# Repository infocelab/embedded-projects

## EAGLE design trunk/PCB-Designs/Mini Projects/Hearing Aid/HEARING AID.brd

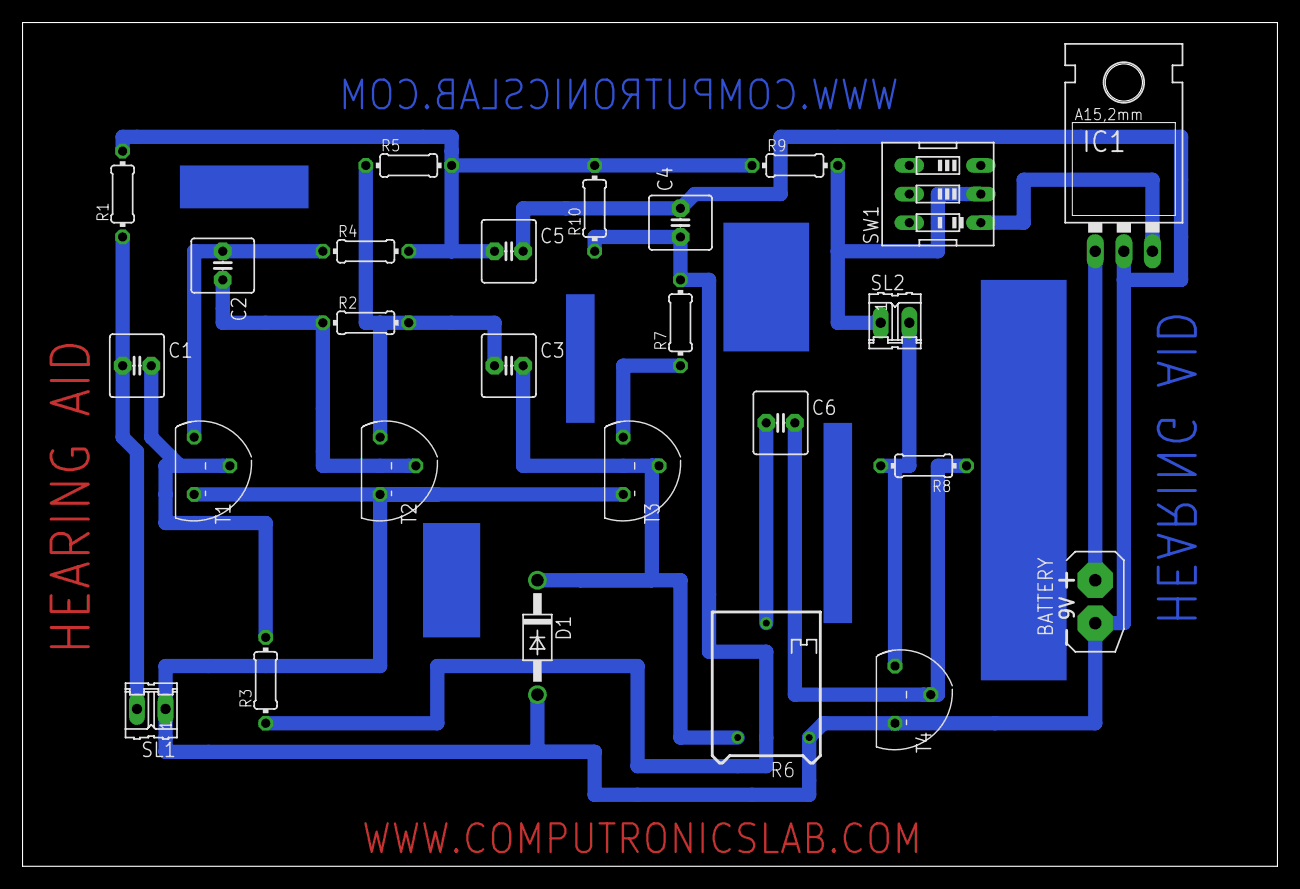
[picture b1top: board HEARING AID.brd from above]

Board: 2 copper layers, 111.4 x 74.9 mm, 26 parts (0 on the bottom side), 16 nets.

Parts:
BATTERY: 9V; AB9V
C1, C2: 0.1uf; C2.5-6
C3, C6: 1uf; C2.5-6
C4: 10uf; C2.5-6
C5: 100uf; C2.5-6
D1: 1N4007; DO41-10
IC1: 7805; 78XXL
R1, R8: 10K; 0204/7
R2, R10: 100k; 0204/7
R3: 1M; 0204/7
R4: 4.7K; 0204/7
R5: 3.9K; 0204/7
R6: 22K; RTRIM64P
R7: 1.5K; 0204/7
R9: 100E; 0204/7
SL1: electret mic; 02P
SL2: ear phone; 02P
SW1: on/off switch; EDG-03
T1, T2, T3, T4: BC547; TO92

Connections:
unnamed: C1.2, R3.2, T1.2
unnamed: C1.1, R1.1, SL1.2
unnamed: C2.1, R4.1, T1.3
unnamed: C2.2, R2.1, T2.2
unnamed: C3.1, R2.2, R5.1, T2.3
unnamed: C3.2, D1.C, R6.3, T3.2
unnamed: R7.1, T3.3
unnamed: C4.1, R3.1, R7.2, R10.1
unnamed: C5.1, R1.2, R4.2, R5.2, R9.1, R10.2
unnamed: C6.1, R6.2
unnamed: C6.2, R8.1, T4.2
unnamed: R8.2, SL2.2, T4.3
unnamed: BATTERY.+, IC1.IN
unnamed: BATTERY.-, C4.2, C5.2, D1.A, IC1.GND, R6.1, SL1.1, T1.1, T2.1, T3.1, T4.1
unnamed: IC1.OUT, SW1.1
unnamed: R9.2, SL2.1, SW1.2

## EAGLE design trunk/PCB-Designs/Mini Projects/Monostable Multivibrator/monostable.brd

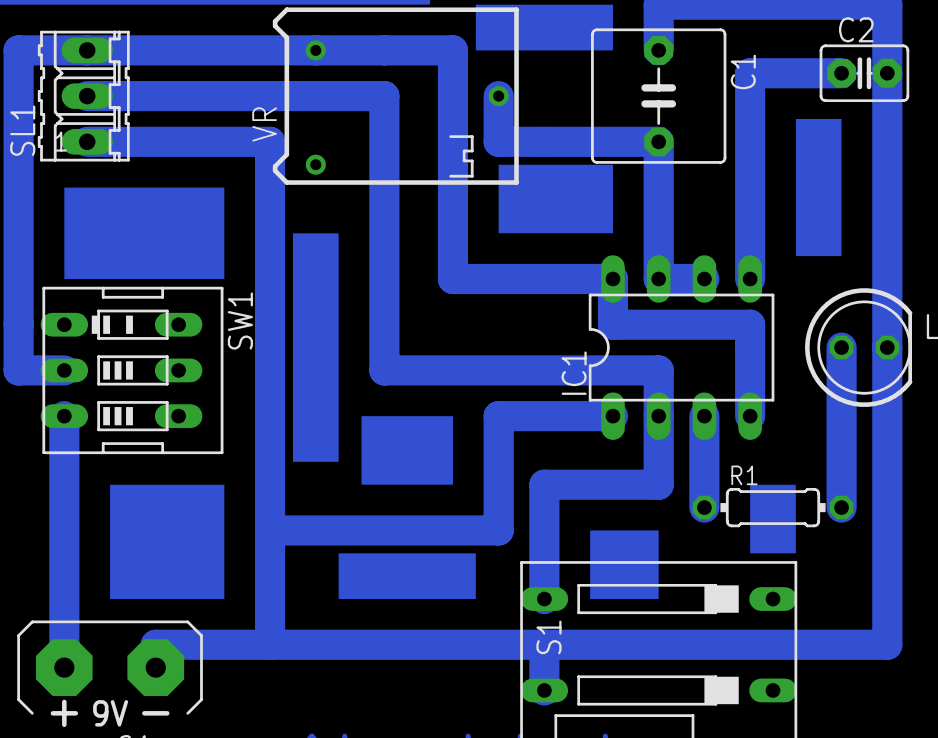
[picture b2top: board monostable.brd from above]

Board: 2 copper layers, 10 parts (0 on the bottom side), 8 nets.

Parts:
C1: 100uf; C5B7.2
C2: 0.1uf; C2.5-3
G1: AB9V
IC1: NE555; DIL-08
LED1: 5mm; LED5MM
R1: 330E; 0204/7
S1: push switch; DS-02
SL1: 03P
SW1: on/off switch; EDG-03
VR: 100k; RTRIM64P

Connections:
unnamed: C1.2, IC1.6, IC1.7, VR.2
unnamed: IC1.2, S1.3, SL1.2
unnamed: C2.1, IC1.5
unnamed: IC1.3, R1.1
unnamed: LED1.A, R1.2
unnamed: G1.+, SW1.3
unnamed: C1.1, C2.2, G1.-, IC1.1, LED1.K, S1.4, SL1.1
unnamed: IC1.4, IC1.8, SL1.3, SW1.2, VR.3

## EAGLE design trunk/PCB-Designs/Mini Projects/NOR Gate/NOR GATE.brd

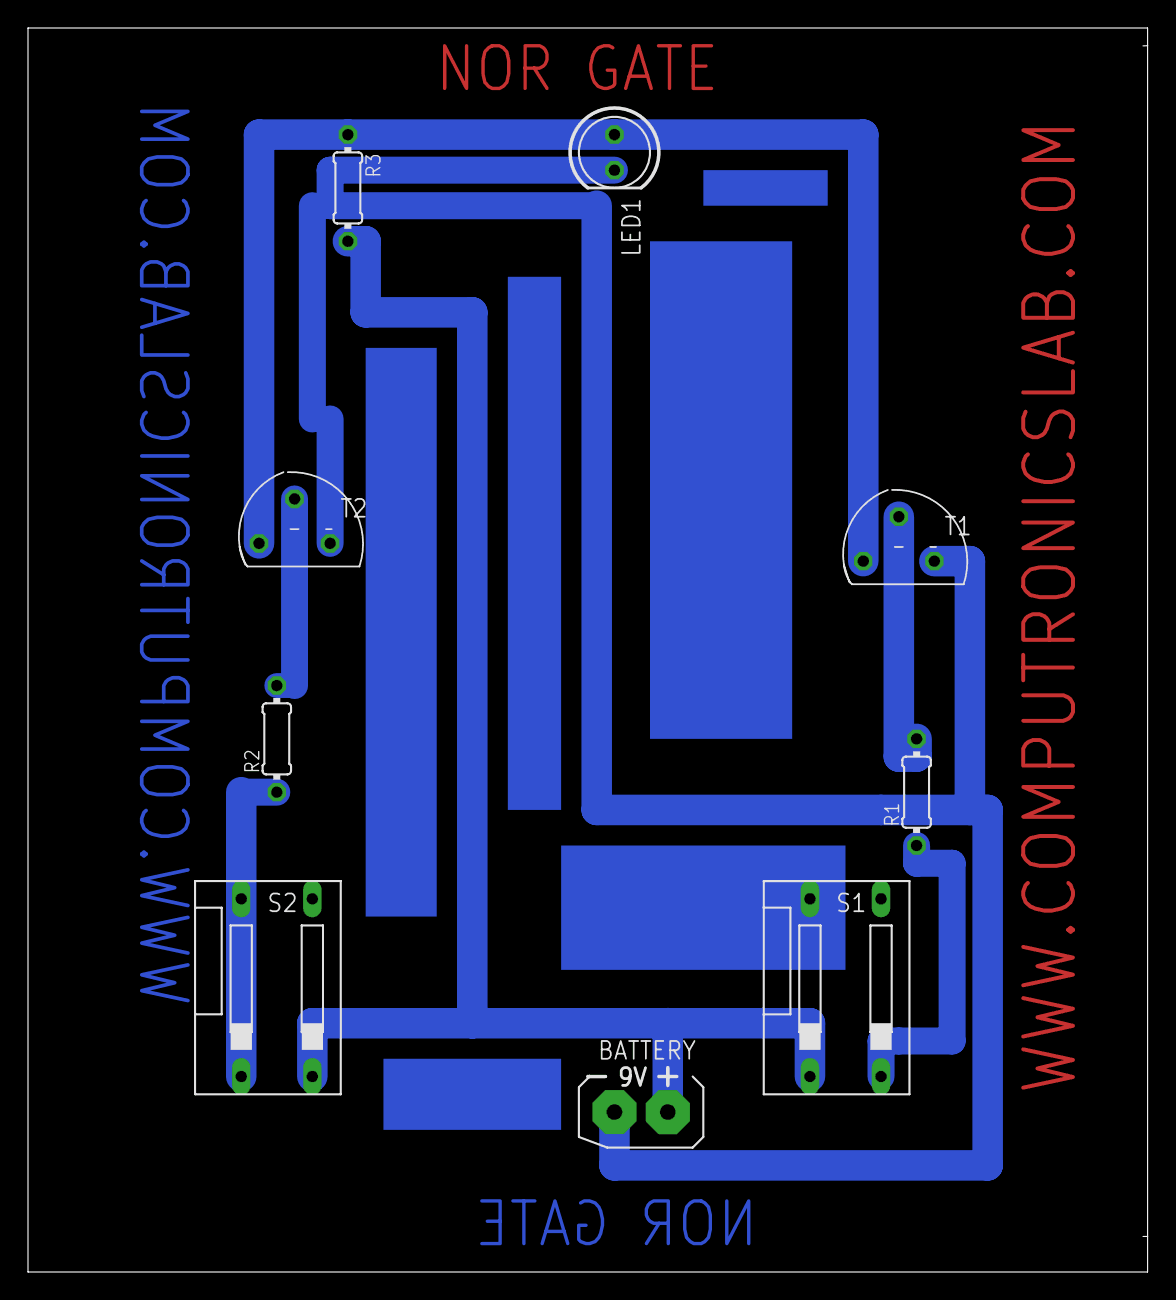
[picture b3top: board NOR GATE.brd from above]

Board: 2 copper layers, 80.0 x 88.9 mm, 9 parts (0 on the bottom side), 7 nets.

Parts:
BATTERY: 9V; AB9V
LED1: LED5MM
R1, R2: 10K; 0204/7
R3: 330E; 0204/7
S1, S2: PUSH SWITCH; DS-02
T1, T2: BC547; TO92

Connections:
unnamed: R1.2, T1.2
unnamed: R2.2, T2.2
unnamed: BATTERY.-, LED1.K, T1.1, T2.1
unnamed: LED1.A, R3.1, T1.3, T2.3
unnamed: R1.1, S1.2
unnamed: R2.1, S2.1
unnamed: BATTERY.+, R3.2, S1.1, S2.2

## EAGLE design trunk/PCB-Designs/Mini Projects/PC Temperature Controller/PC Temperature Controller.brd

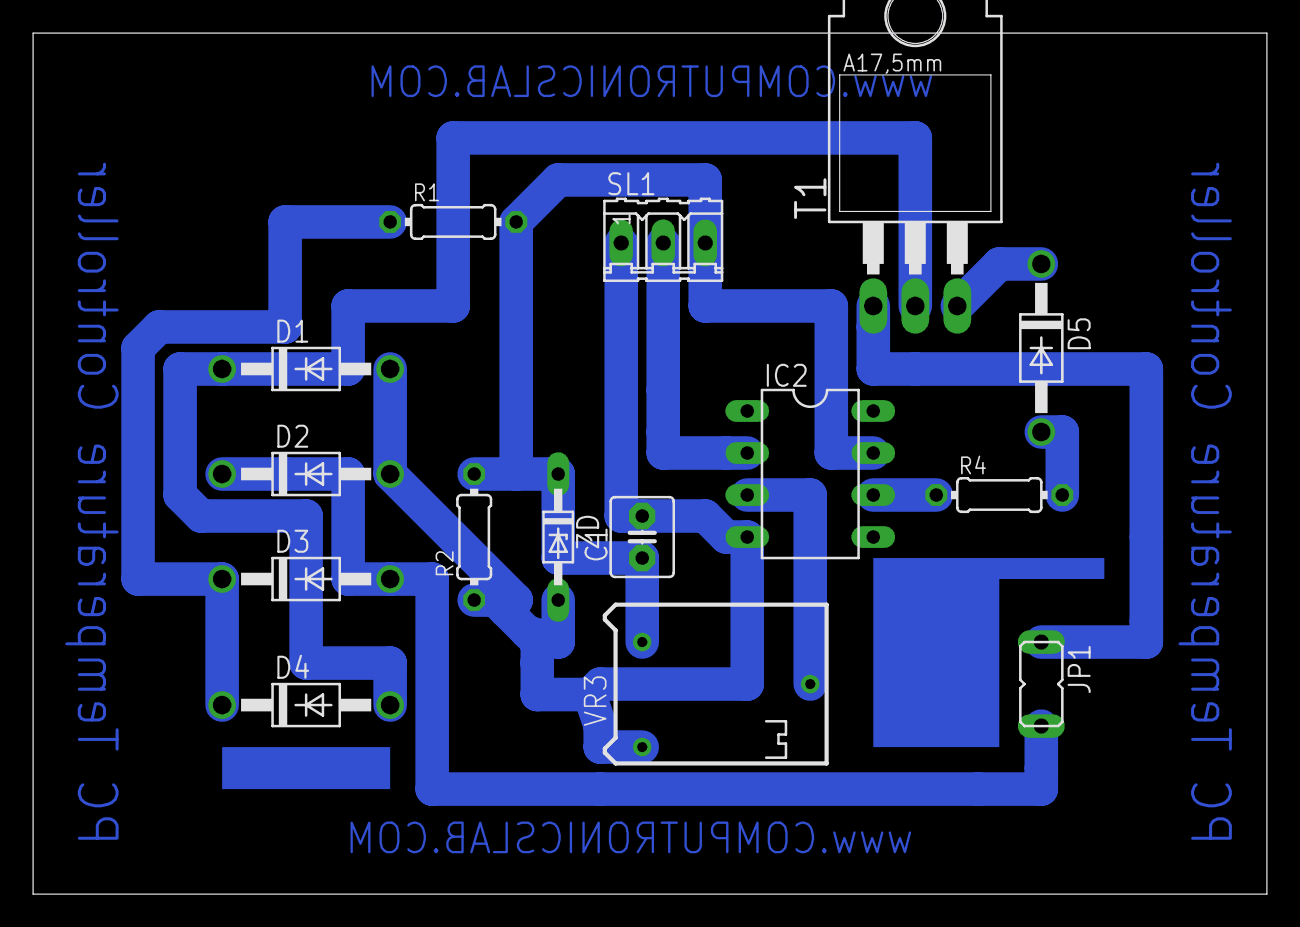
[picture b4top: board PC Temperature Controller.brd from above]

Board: 2 copper layers, 74.6 x 52.1 mm, 15 parts (0 on the bottom side), 11 nets.

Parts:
C1: 100uf; C2.5-4
D1, D2, D3, D4, D5: 1N4007; DO41-10
IC2: ca3140; DIL08
JP1: load; JP1
R1: 33k; 0204/7
R2: 10k; 0204/7
R4: 120E; 0204/7
SL1: lm35; 03P
T1: BT136; TO220AB
VR3: 10k; RTRIM64P
ZD: 9v; DO34Z7

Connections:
unnamed: IC2.6, R4.1
unnamed: D5.A, R4.2
unnamed: D5.C, T1.3
unnamed: C1.2, D1.A, D2.A, IC2.4, R2.1, SL1.1, VR3.1, ZD.A
unnamed: D3.C, D4.C, R1.1
unnamed: D2.C, D3.A, JP1.2
unnamed: D1.C, D4.A, T1.2
unnamed: C1.1, IC2.7, R1.2, R2.2, SL1.3, VR3.3, ZD.C
unnamed: IC2.3, VR3.2
unnamed: IC2.2, SL1.2
unnamed: JP1.1, T1.1

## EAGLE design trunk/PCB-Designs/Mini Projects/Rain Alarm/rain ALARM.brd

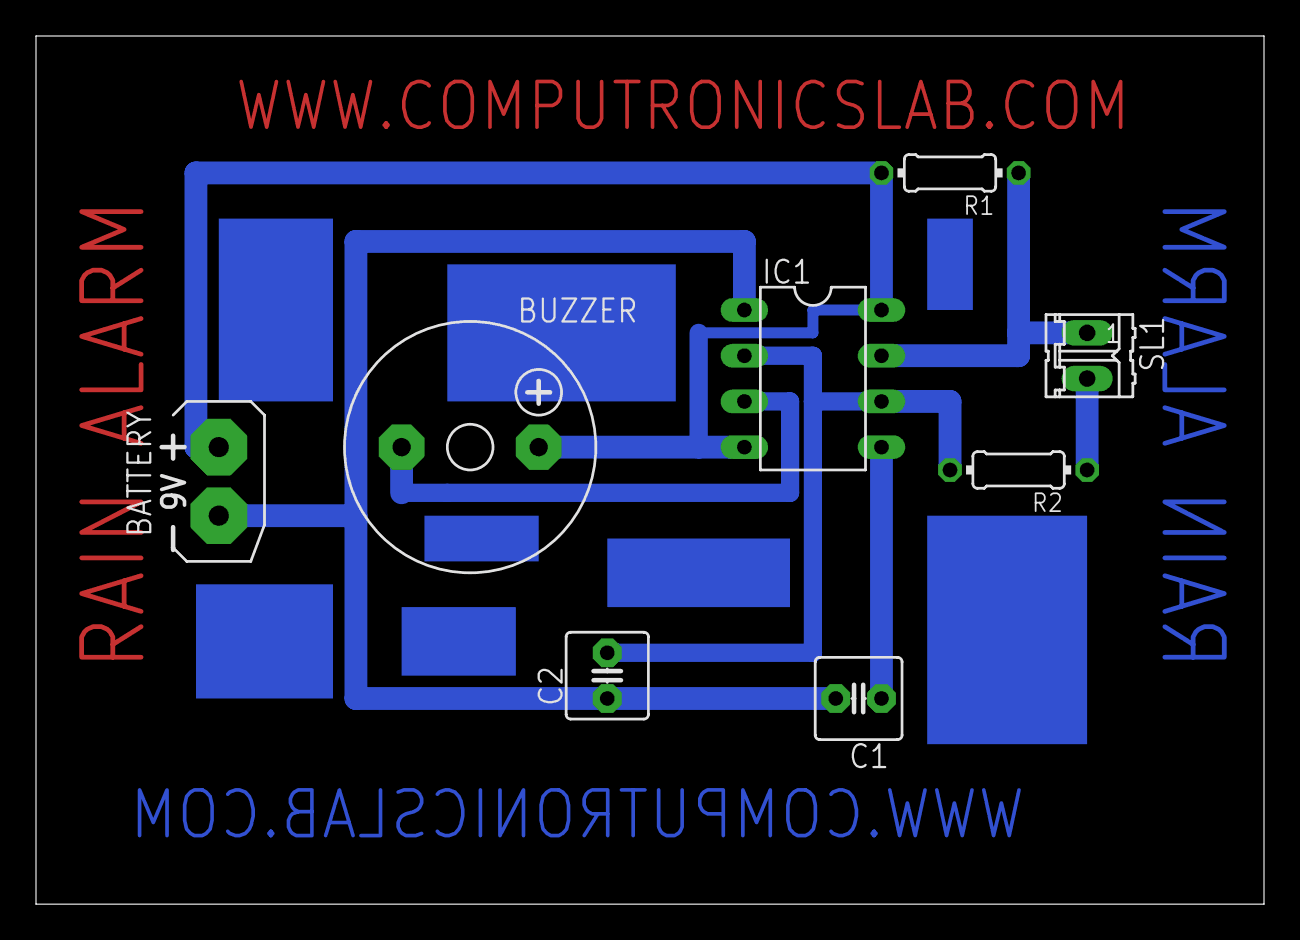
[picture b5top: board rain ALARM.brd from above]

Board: 2 copper layers, 68.2 x 48.2 mm, 8 parts (0 on the bottom side), 7 nets.

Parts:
BATTERY: 9V; AB9V
BUZZER: F/CM12P
C1, C2: 0.01uf; C2.5-5
IC1: NE555; DIL-08
R1: 1k; 0204/7
R2: 47k; 0204/7
SL1: RAIN SENSOR; 02P

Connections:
unnamed: BUZZER.-, IC1.3
unnamed: BATTERY.-, C1.2, C2.1, IC1.1
unnamed: IC1.7, R1.1, SL1.1
unnamed: BATTERY.+, BUZZER.+, IC1.4, IC1.8, R1.2
unnamed: C1.1, IC1.5
unnamed: C2.2, IC1.2, IC1.6, R2.2
unnamed: R2.1, SL1.2

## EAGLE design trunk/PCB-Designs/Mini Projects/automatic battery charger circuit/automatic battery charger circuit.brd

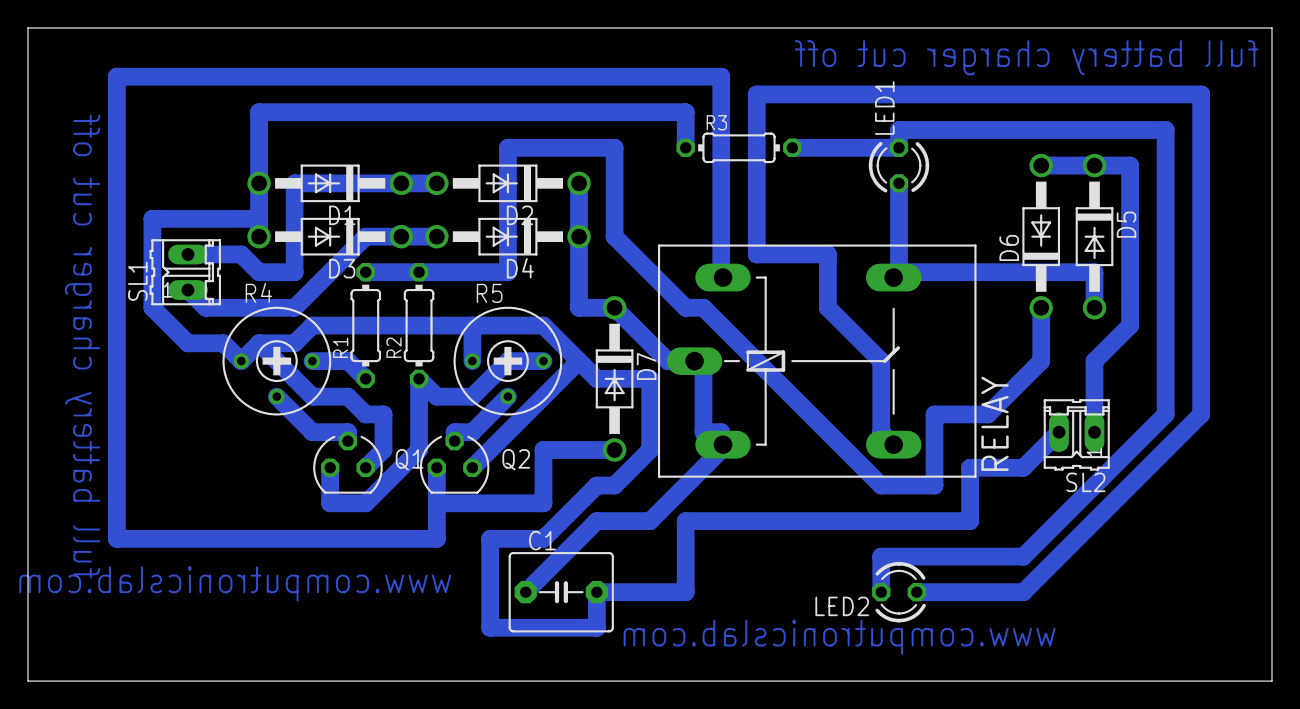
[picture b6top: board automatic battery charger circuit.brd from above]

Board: 2 copper layers, 88.9 x 46.7 mm, 20 parts (0 on the bottom side), 14 nets.

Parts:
C1: 2200uf; C5B5.5
D1, D2, D3, D4, D5, D6, D7: 1N4007; DO41-10
LED1, LED2: 3mm; LED3MM
Q1, Q2: BC547; SOT54A
R1, R2: 10K; 0204/7
R3: 220R; 0204/7
R4, R5: 10K; RTRIM3339P
RELAY: 6v; G5LE
SL1: transformer; 02P
SL2: battery; 02P

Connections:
unnamed: D1.C, D2.A, SL1.2
unnamed: D3.C, D4.A, SL1.1
unnamed: C1.2, D1.A, D3.A, Q1.E, Q2.E, R3.1, R4.1, R5.1, SL2.2
unnamed: C1.1, D2.C, D4.C, D7.C, RELAY.1, RELAY.P
unnamed: Q1.B, R4.2
unnamed: R1.1, R4.3
unnamed: Q1.C, R2.1, R5.3
unnamed: Q2.B, R5.2
unnamed: D6.C, R1.2, R2.2
unnamed: D5.A, LED1.A, RELAY.O
unnamed: D7.A, Q2.C, RELAY.2
unnamed: D5.C, D6.A, SL2.1
unnamed: LED1.K, LED2.K, R3.2
unnamed: LED2.A, RELAY.S

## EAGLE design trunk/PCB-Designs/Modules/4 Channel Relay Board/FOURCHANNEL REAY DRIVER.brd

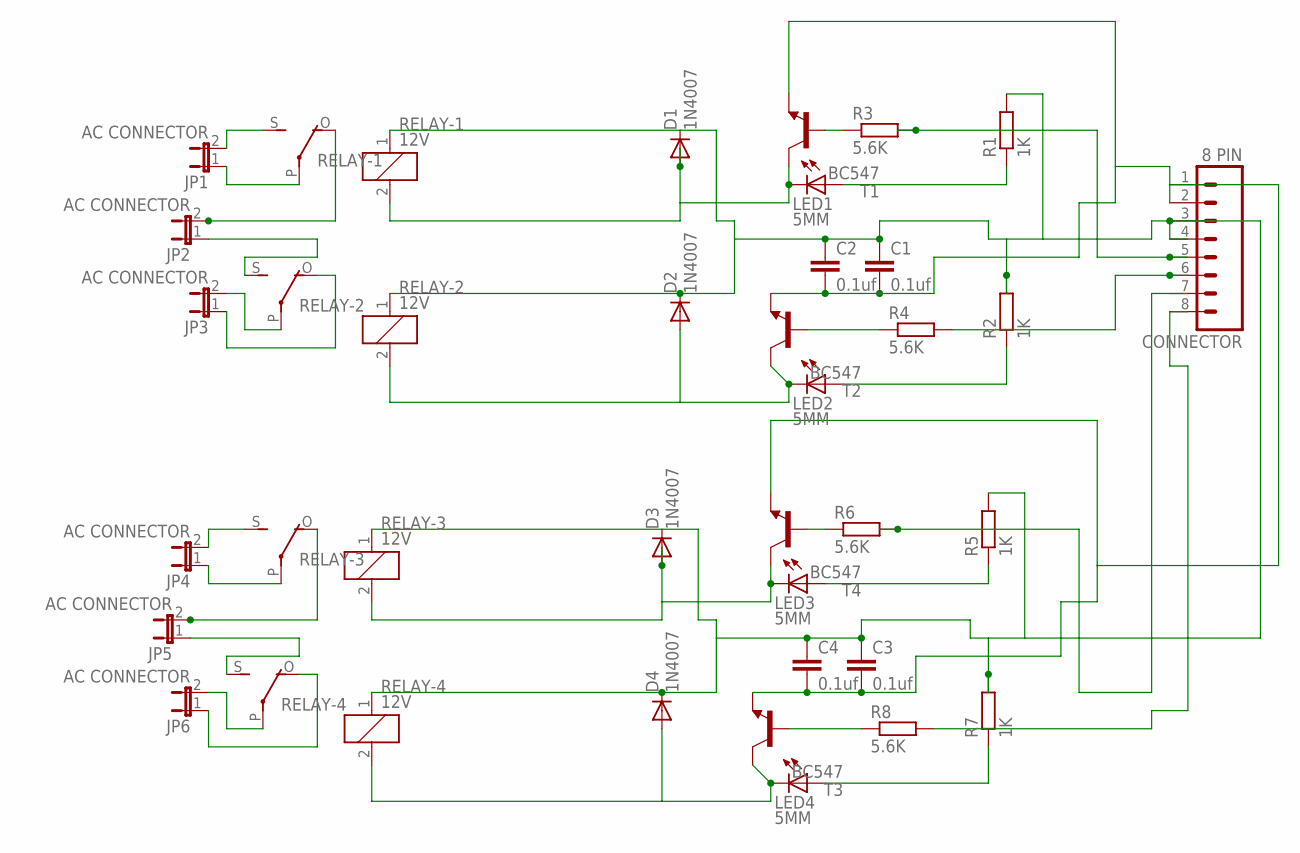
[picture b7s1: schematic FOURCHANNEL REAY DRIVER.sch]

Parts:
C1, C2, C3, C4: 0.1uf; C2.5-3
CONNECTOR: 8 PIN; 08P
D1, D2, D3, D4: 1N4007; DO41-10
JP1, JP2, JP3, JP4, JP5, JP6: AC CONNECTOR; JP1
LED1, LED2, LED3, LED4: 5MM; LED5MM
R1, R2, R5, R7: 1K; 0204/7
R3, R4, R6, R8: 5.6K; 0204/7
RELAY-1, RELAY-2, RELAY-3, RELAY-4: 12V; G5LE
T1, T2, T3, T4: BC547; TO92

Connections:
unnamed: D1.A, LED1.K (C), RELAY-1.2, T1.3 (C)
unnamed: D3.A, LED3.K (C), RELAY-3.2, T4.3 (C)
unnamed: C1.1, C2.1, C3.1, C4.1, CONNECTOR.3, CONNECTOR.4, D1.C, D2.C, D3.C, D4.C, R1.2, R2.2, R5.2, R7.2, RELAY-1.1, RELAY-2.1, RELAY-3.1, RELAY-4.1
unnamed: R4.1, T2.2 (B)
unnamed: R3.1, T1.2 (B)
unnamed: LED1.A, R1.1
unnamed: LED2.A, R2.1
unnamed: JP1.2, RELAY-1.S
unnamed: JP1.1, RELAY-1.P
unnamed: JP2.2, RELAY-1.O
unnamed: JP2.1, RELAY-2.S
unnamed: JP3.2, RELAY-2.P
unnamed: JP3.1, RELAY-2.O
unnamed: R8.1, T3.2 (B)
unnamed: CONNECTOR.5, R3.2
unnamed: CONNECTOR.6, R4.2
unnamed: R6.1, T4.2 (B)
unnamed: D2.A, LED2.K (C), RELAY-2.2, T2.3 (C)
unnamed: LED3.A, R5.1
unnamed: LED4.A, R7.1
unnamed: JP4.2, RELAY-3.S
unnamed: JP4.1, RELAY-3.P
unnamed: JP5.2, RELAY-3.O
unnamed: JP5.1, RELAY-4.S
unnamed: JP6.2, RELAY-4.P
unnamed: JP6.1, RELAY-4.O
unnamed: C1.2, C2.2, C3.2, C4.2, CONNECTOR.1, CONNECTOR.2, T1.1 (E), T2.1 (E), T3.1 (E), T4.1 (E)
unnamed: CONNECTOR.7, R6.2
unnamed: CONNECTOR.8, R8.2
unnamed: D4.A, LED4.K (C), RELAY-4.2, T3.3 (C)

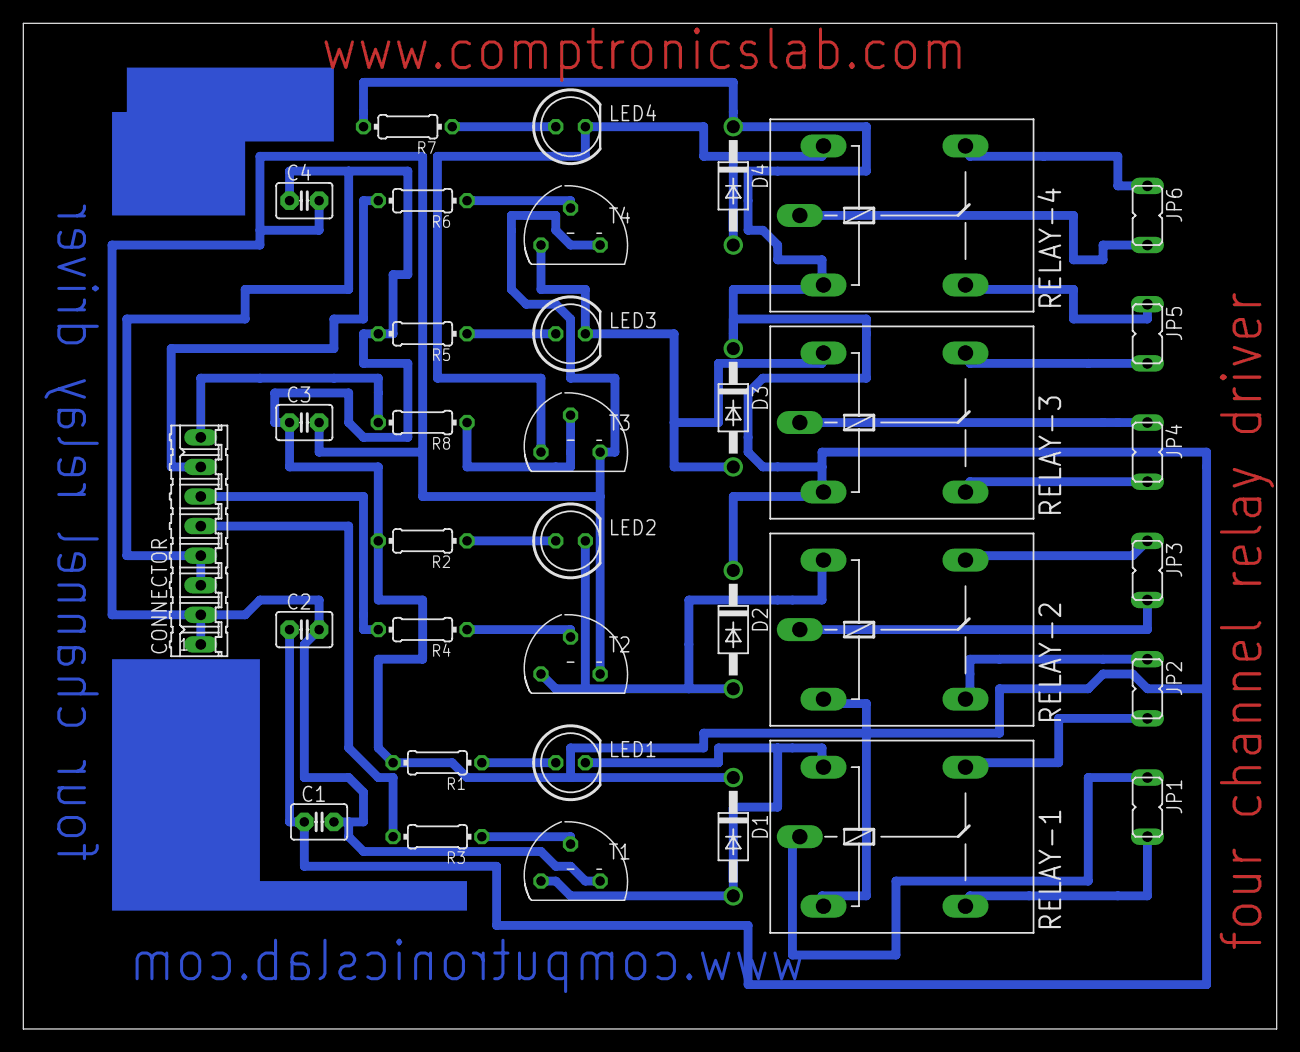
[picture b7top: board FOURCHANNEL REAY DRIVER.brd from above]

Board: 2 copper layers, 107.6 x 86.4 mm, 35 parts (0 on the bottom side), 30 nets.
